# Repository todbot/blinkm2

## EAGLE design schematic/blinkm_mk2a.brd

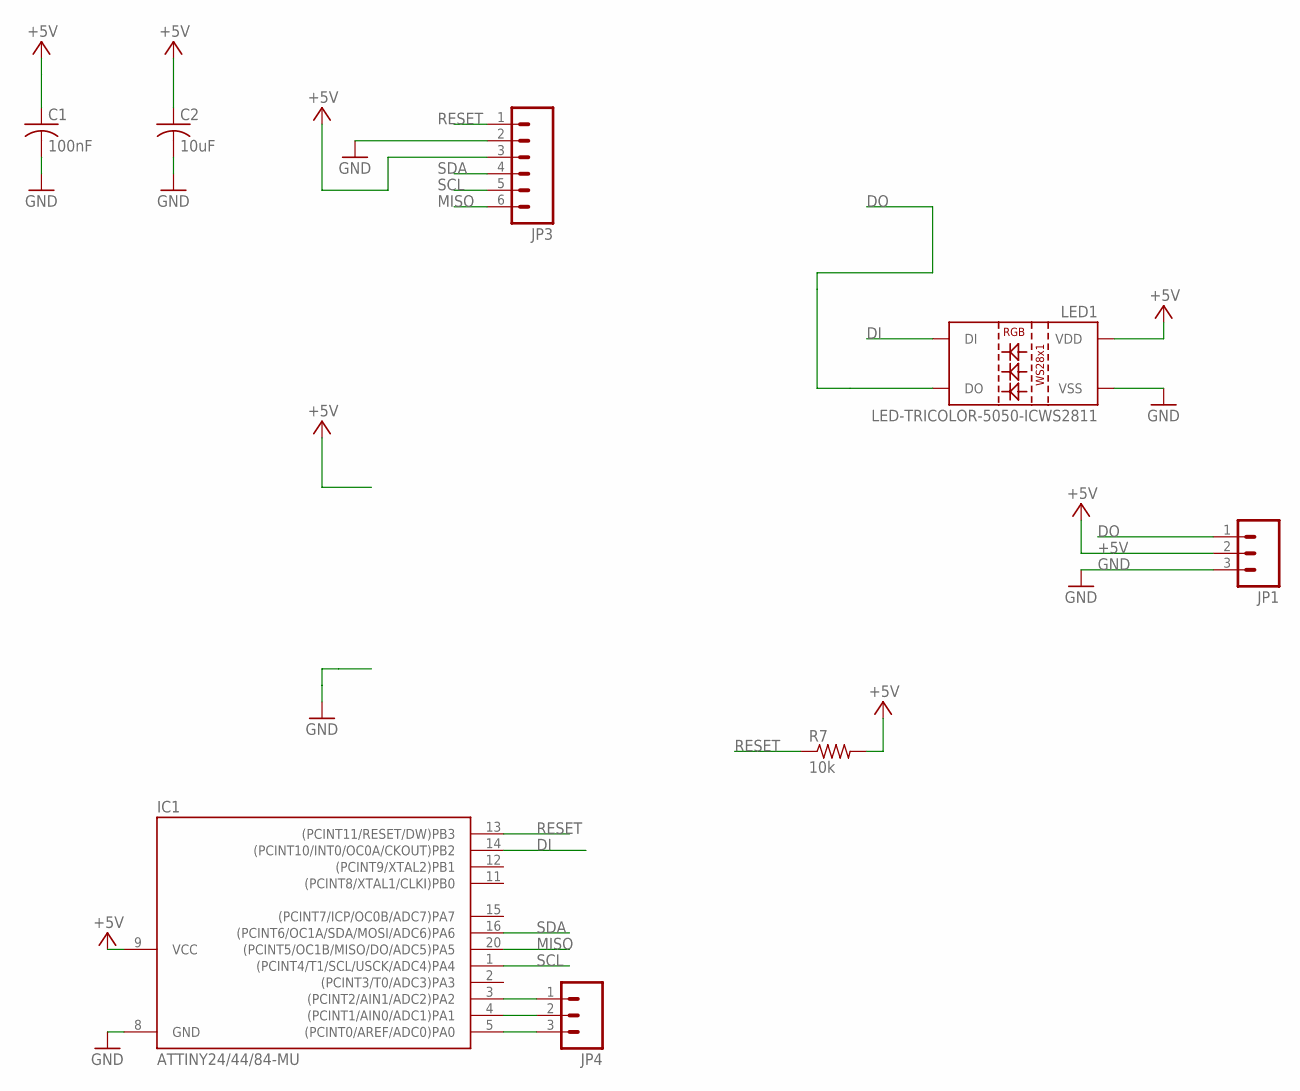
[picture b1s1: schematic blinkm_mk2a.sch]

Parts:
C1: 100nF; C0603
C2: 10uF; C0603
IC1: ATTINY24/44/84-MU; QFN/MLF20
JP1, JP4: M03PTH; 1X03
JP3: M06SIP; 1X06
LED1: LED-TRICOLOR-5050-ICWS2811; LED-TRICOLOR-5050-IC
R7: 10k; R0603

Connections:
+5V: C1.1, C2.1, IC1.9 (VCC), JP1.2, JP3.3, LED1.3 (VDD), LED1.5 (VDD), R7.2
DI: IC1.14 ((PCINT10/INT0/OC0A/CKOUT)PB2), LED1.2 (DI)
DO: JP1.1, LED1.1 (DO)
GND: C1.2, C2.2, IC1.8 (GND), JP1.3, JP3.2, LED1.6 (VSS)
MISO: IC1.20 ((PCINT5/OC1B/MISO/DO/ADC5)PA5), JP3.6
unnamed: IC1.3 ((PCINT2/AIN1/ADC2)PA2), JP4.1
unnamed: IC1.4 ((PCINT1/AIN0/ADC1)PA1), JP4.2
unnamed: IC1.5 ((PCINT0/AREF/ADC0)PA0), JP4.3
RESET: IC1.13 ((PCINT11/RESET/DW)PB3), JP3.1, R7.1
SCL: IC1.1 ((PCINT4/T1/SCL/USCK/ADC4)PA4), JP3.5
SDA: IC1.16 ((PCINT6/OC1A/SDA/MOSI/ADC6)PA6), JP3.4

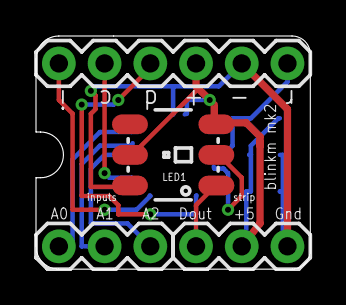
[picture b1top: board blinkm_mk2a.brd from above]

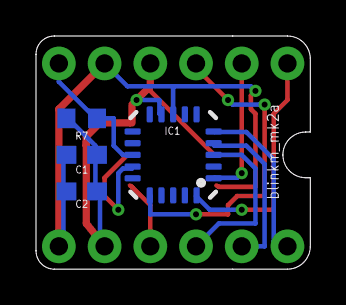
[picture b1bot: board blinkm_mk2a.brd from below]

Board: 2 copper layers, 15.2 x 13.0 mm, 8 parts (4 on the bottom side), 11 nets.

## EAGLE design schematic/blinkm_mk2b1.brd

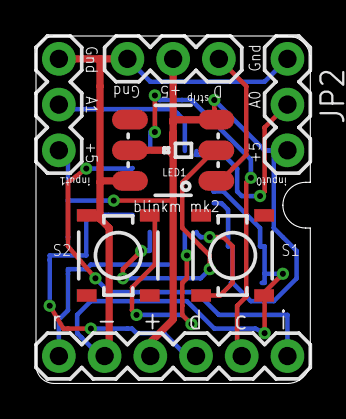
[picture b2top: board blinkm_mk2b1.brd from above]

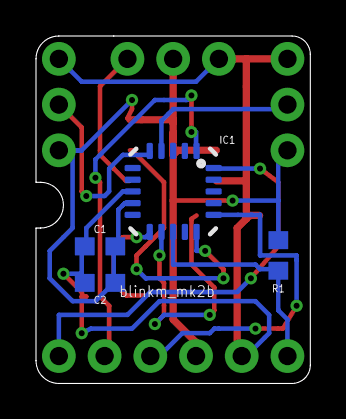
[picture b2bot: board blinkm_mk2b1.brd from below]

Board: 2 copper layers, 15.2 x 19.3 mm, 11 parts (4 on the bottom side), 12 nets.

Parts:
C1: 100nF; C0603
C2: 10uF; C0603
IC1: ATTINY24/44/84-MU; QFN/MLF20
JP1: strip; 1X03
JP2: input0; 1X03
JP3: input1; 1X03
JP4: 1X06
LED1: LED-TRICOLOR-5050-ICWS2811; LED-TRICOLOR-5050-IC
R1: 10k; R0603
S1, S2: SWITCH-MOMENTARY-2SMD-2; TACTILE_SWITCH_SMD-2

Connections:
+5V: C1.1, C2.1, IC1.9, JP1.2, JP2.3, JP3.3, JP4.3, LED1.3, LED1.5, R1.2
A0: IC1.5, JP2.2
A1: IC1.4, JP3.2
DI: IC1.15, LED1.2
DO: JP1.1, LED1.1
GND: C1.2, C2.2, IC1.8, JP1.3, JP2.1, JP3.1, JP4.2, LED1.6, S1.1, S2.1
MISO: IC1.20, JP4.6
RESET: IC1.13, JP4.1, R1.1
S1: IC1.11, S1.2
S2: IC1.12, S2.2
SCL: IC1.1, JP4.5
SDA: IC1.16, JP4.4

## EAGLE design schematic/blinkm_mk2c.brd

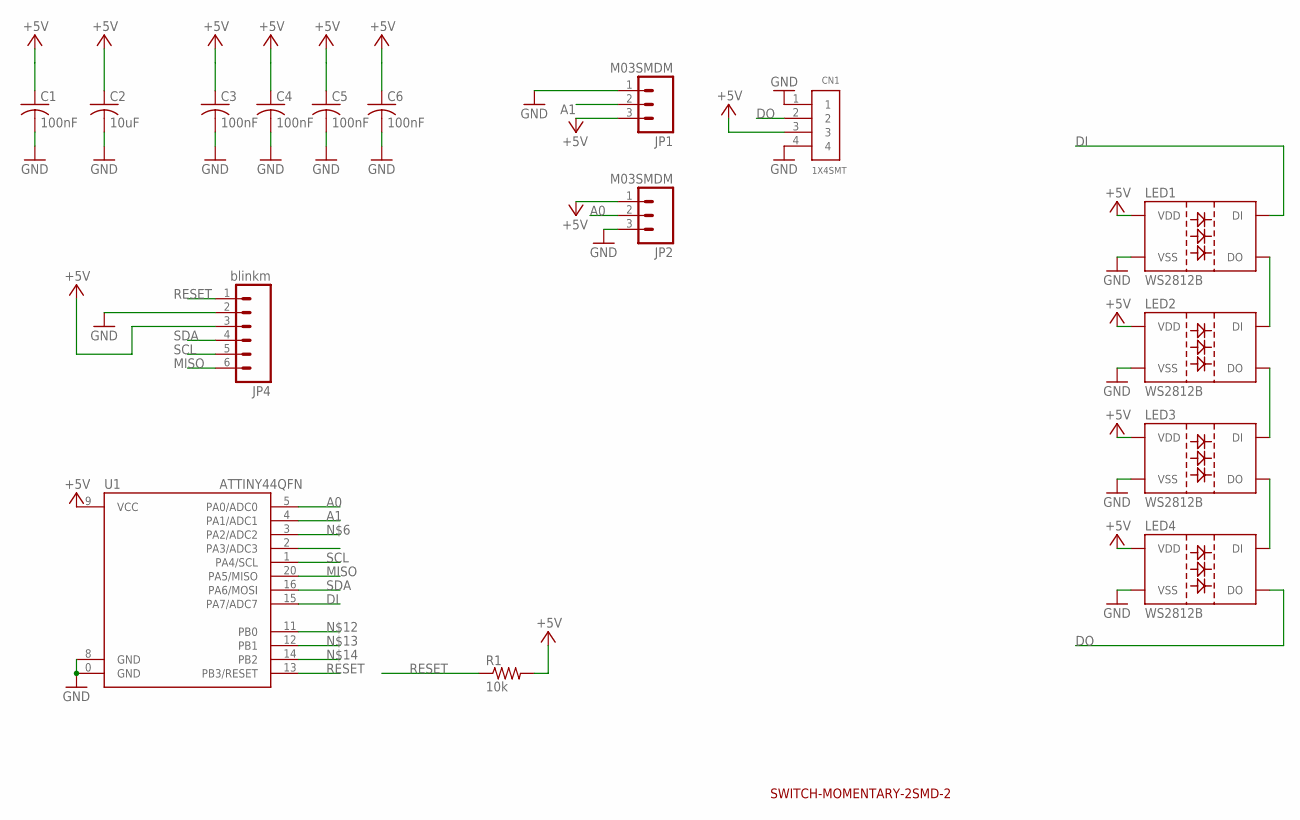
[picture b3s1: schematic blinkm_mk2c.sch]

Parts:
C1, C3, C4, C5, C6: 100nF; C0603
C2: 10uF; C0603
CN1: 1X4SMT; 1X4-SMT
JP1, JP2: M03SMDM; 1X03-SMD-MINIMAL
JP4: blinkm; 1X06_LOCK
LED1, LED2, LED3, LED4: WS2812B
R1: 10k; R0603
U1: ATTINY44QFN; QFN20

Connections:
+5V: C1.1, C2.1, C3.1, C4.1, C5.1, C6.1, CN1.3, JP1.3, JP2.1, JP4.3, LED1.1 (VDD), LED2.1 (VDD), LED3.1 (VDD), LED4.1 (VDD), R1.2, U1.9 (VCC)
A0: JP2.2, U1.5 (PA0/ADC0)
A1: JP1.2, U1.4 (PA1/ADC1)
DI: LED1.4 (DI), U1.15 (PA7/ADC7); also elsewhere on the board
DO: CN1.2, LED4.2 (DO)
GND: C1.2, C2.2, C3.2, C4.2, C5.2, C6.2, CN1.1, CN1.4, JP1.1, JP2.3, JP4.2, LED1.3 (VSS), LED2.3 (VSS), LED3.3 (VSS), LED4.3 (VSS), U1.0 (GND), U1.8 (GND); also elsewhere on the board
MISO: JP4.6, U1.20 (PA5/MISO)
unnamed: LED1.2 (DO), LED2.4 (DI)
unnamed: LED2.2 (DO), LED3.4 (DI)
unnamed: LED3.2 (DO), LED4.4 (DI)
RESET: JP4.1, R1.1, U1.13 (PB3/RESET)
SCL: JP4.5, U1.1 (PA4/SCL)
SDA: JP4.4, U1.16 (PA6/MOSI)

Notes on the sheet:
SWITCH-MOMENTARY-2SMD-2

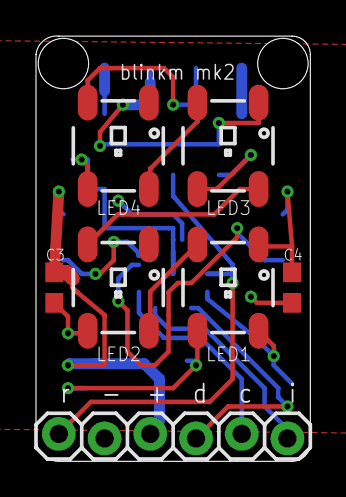
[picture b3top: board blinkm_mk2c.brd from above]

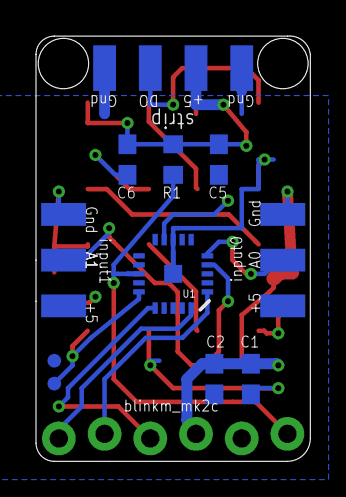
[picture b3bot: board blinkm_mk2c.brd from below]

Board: 2 copper layers, 15.2 x 23.6 mm, 18 parts (11 on the bottom side), 13 nets.

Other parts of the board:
TP1, TP2: TEST-POINT3; PAD.03X.03

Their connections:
DI: TP1.P$1; also elsewhere on the board
GND: TP2.P$1; also elsewhere on the board

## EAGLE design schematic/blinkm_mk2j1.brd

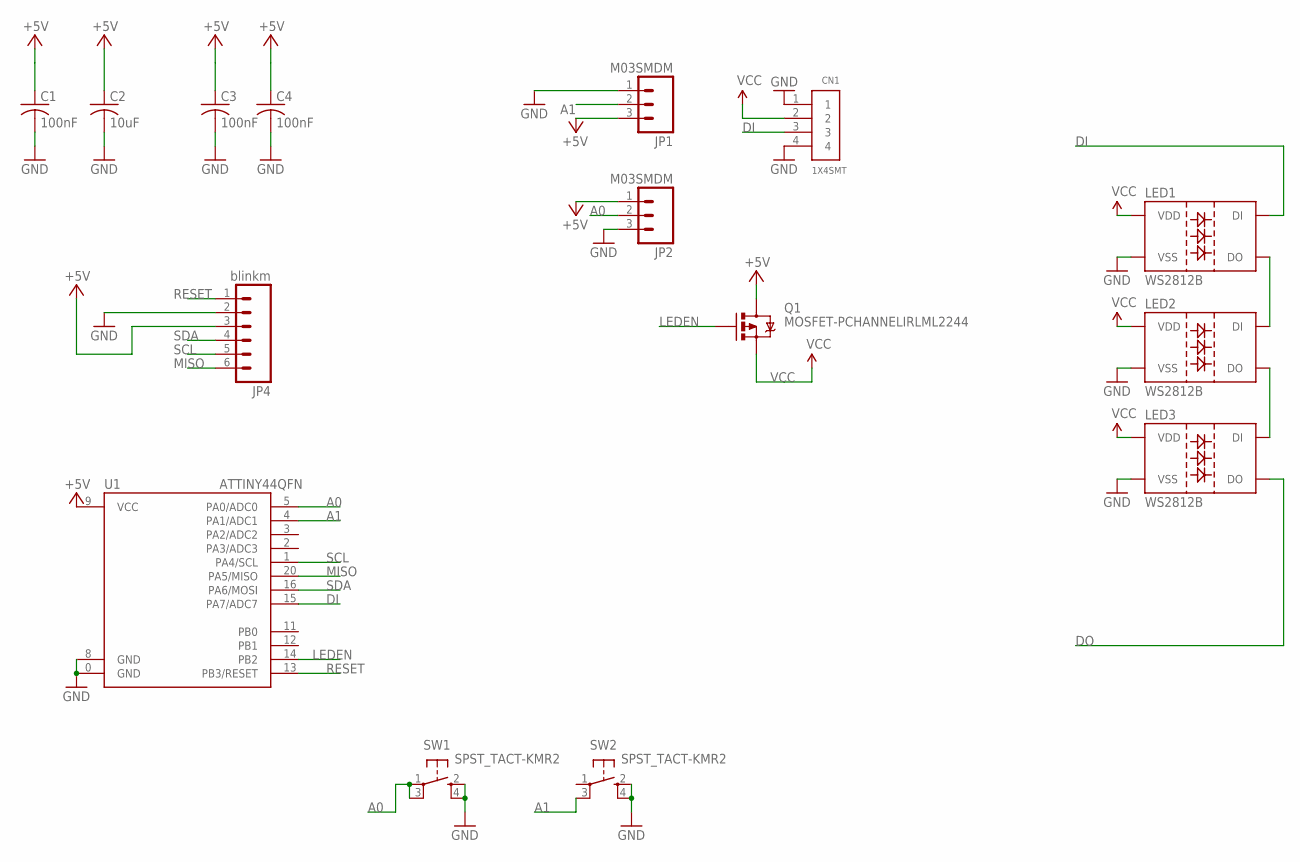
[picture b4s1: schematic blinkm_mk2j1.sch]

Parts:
C1, C3, C4: 100nF; C0603
C2: 10uF; C0603
CN1: 1X4SMT; 1X4-SMT
JP1, JP2: M03SMDM; 1X03-SMD-MINIMAL
JP4: blinkm; 1X06_LOCK
LED1, LED2, LED3: WS2812B
Q1: MOSFET-PCHANNELIRLML2244; SOT23-3
SW1, SW2: SPST_TACT-KMR2; KMR2
U1: ATTINY44QFN; QFN20

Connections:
+5V: C1.1, C2.1, C3.1, C4.1, JP1.3, JP2.1, JP4.3, Q1.3 (D), U1.9 (VCC)
A0: JP2.2, SW1.1, SW1.3 (P1), U1.5 (PA0/ADC0)
A1: JP1.2, SW2.3 (P1), U1.4 (PA1/ADC1)
DI: CN1.3, LED1.4 (DI), U1.15 (PA7/ADC7)
DO: LED3.2 (DO)
DOI1: LED1.2 (DO), LED2.4 (DI)
DOI2: LED2.2 (DO), LED3.4 (DI)
GND: C1.2, C2.2, C3.2, C4.2, CN1.1, CN1.4, JP1.1, JP2.3, JP4.2, LED1.3 (VSS), LED2.3 (VSS), LED3.3 (VSS), SW1.2 (S), SW1.4 (S1), SW2.2 (S), SW2.4 (S1), U1.0 (GND), U1.8 (GND)
LEDEN: Q1.1 (G), U1.14 (PB2)
MISO: JP4.6, U1.20 (PA5/MISO)
RESET: JP4.1, U1.13 (PB3/RESET)
SCL: JP4.5, U1.1 (PA4/SCL)
SDA: JP4.4, U1.16 (PA6/MOSI)
VCC: CN1.2, LED1.1 (VDD), LED2.1 (VDD), LED3.1 (VDD), Q1.2 (S)

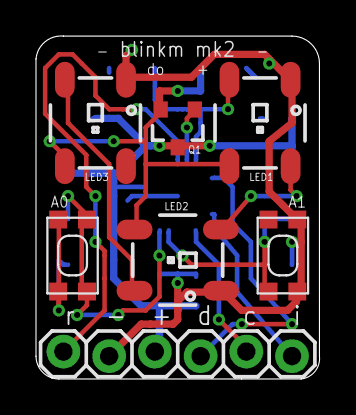
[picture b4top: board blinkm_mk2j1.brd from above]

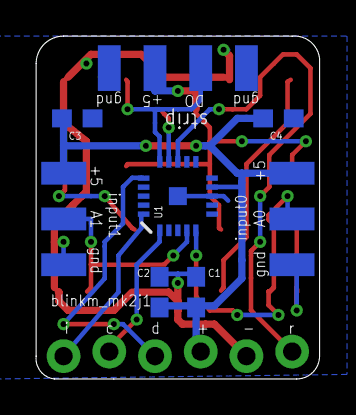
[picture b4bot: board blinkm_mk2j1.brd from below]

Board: 2 copper layers, 15.8 x 19.1 mm, 15 parts (8 on the bottom side), 13 nets.

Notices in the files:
parts and their libraries:
SparkFun-LED: Licensing: CC v3.0 Share-Alike You are welcome to use this library for commercial purposes.
